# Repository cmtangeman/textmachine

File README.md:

# TextMachine
CrankPhone SW/FW/HW/Mech
Notes on directory structure:

FW:

ArduinoILI9341MKNNB1500 :  All for resistive touch FW (old)

capTouchTestingAndCal: testing calibration of capacitive touch

receiveSMSwithDebug:  debug file that doesn't need touchscreen

techmach: FW for old resistive screen

techmachcap: FW for current working capacitive touch screen.  See README.txt in this directory for further info.

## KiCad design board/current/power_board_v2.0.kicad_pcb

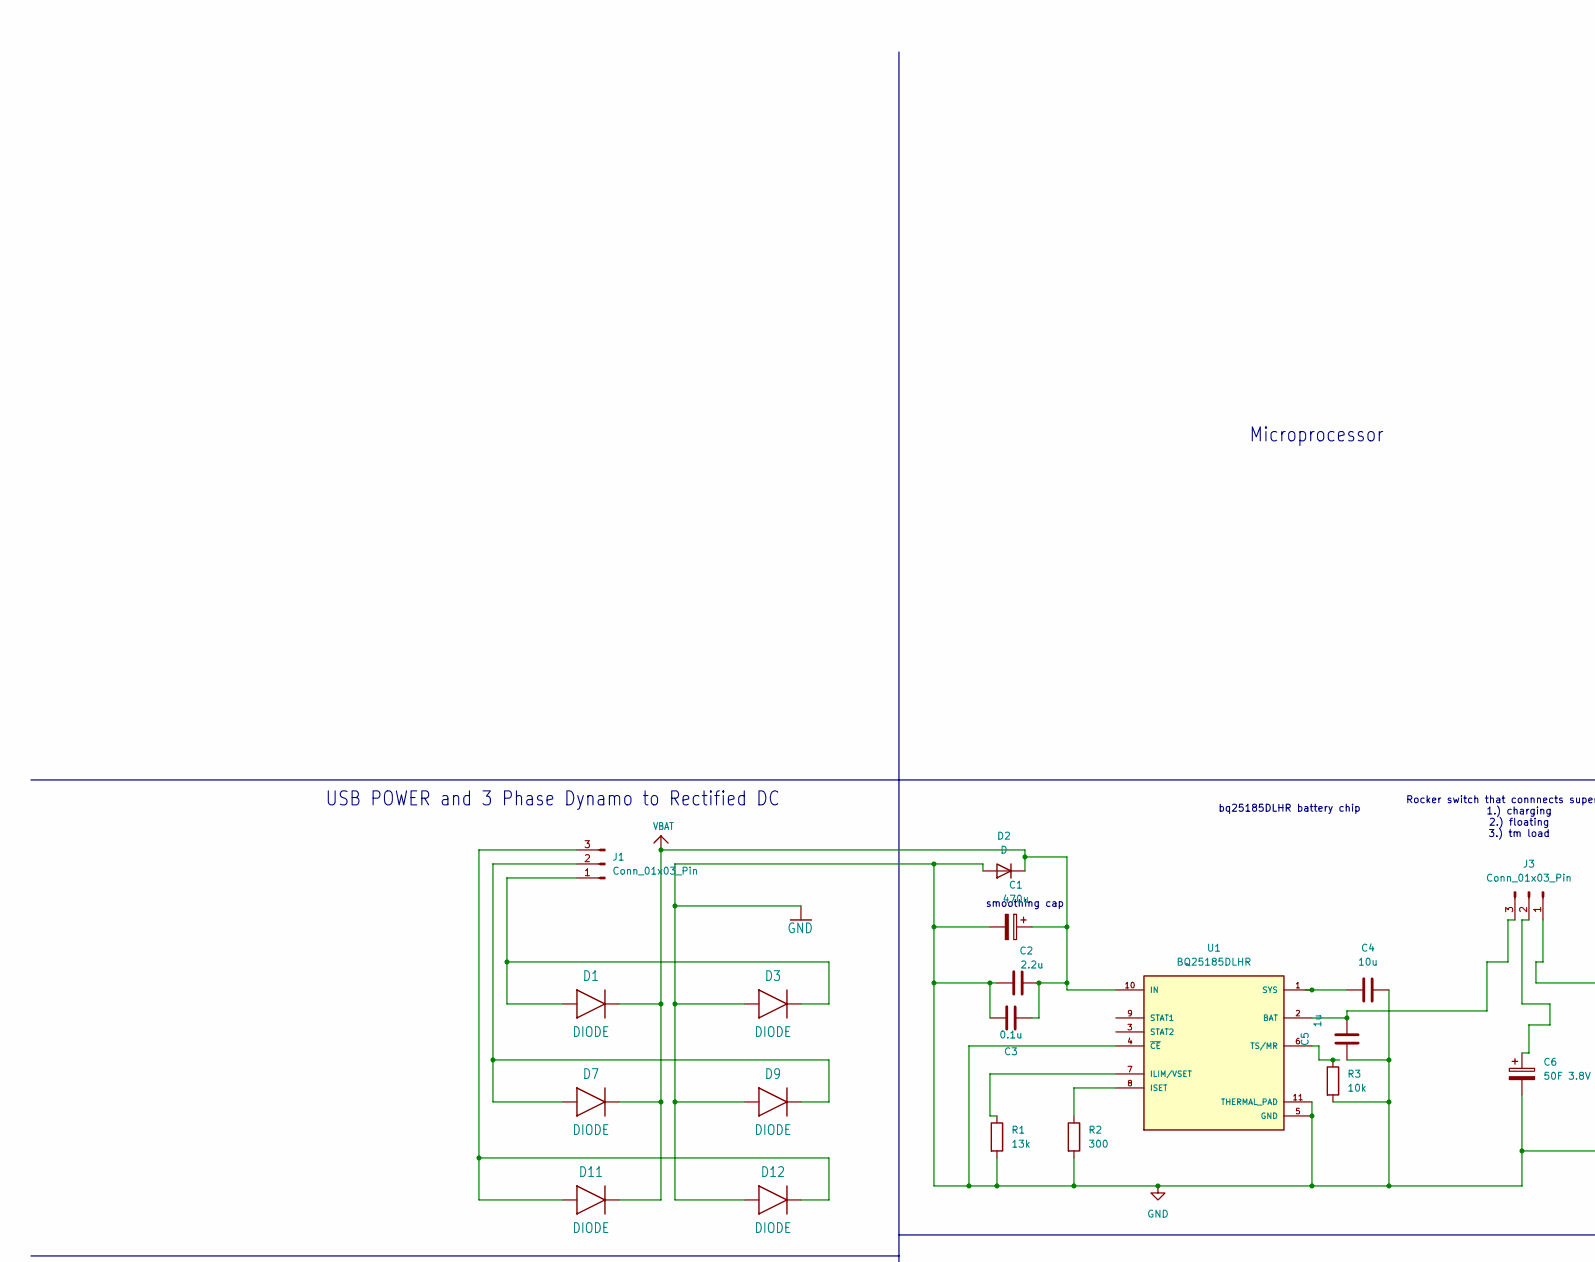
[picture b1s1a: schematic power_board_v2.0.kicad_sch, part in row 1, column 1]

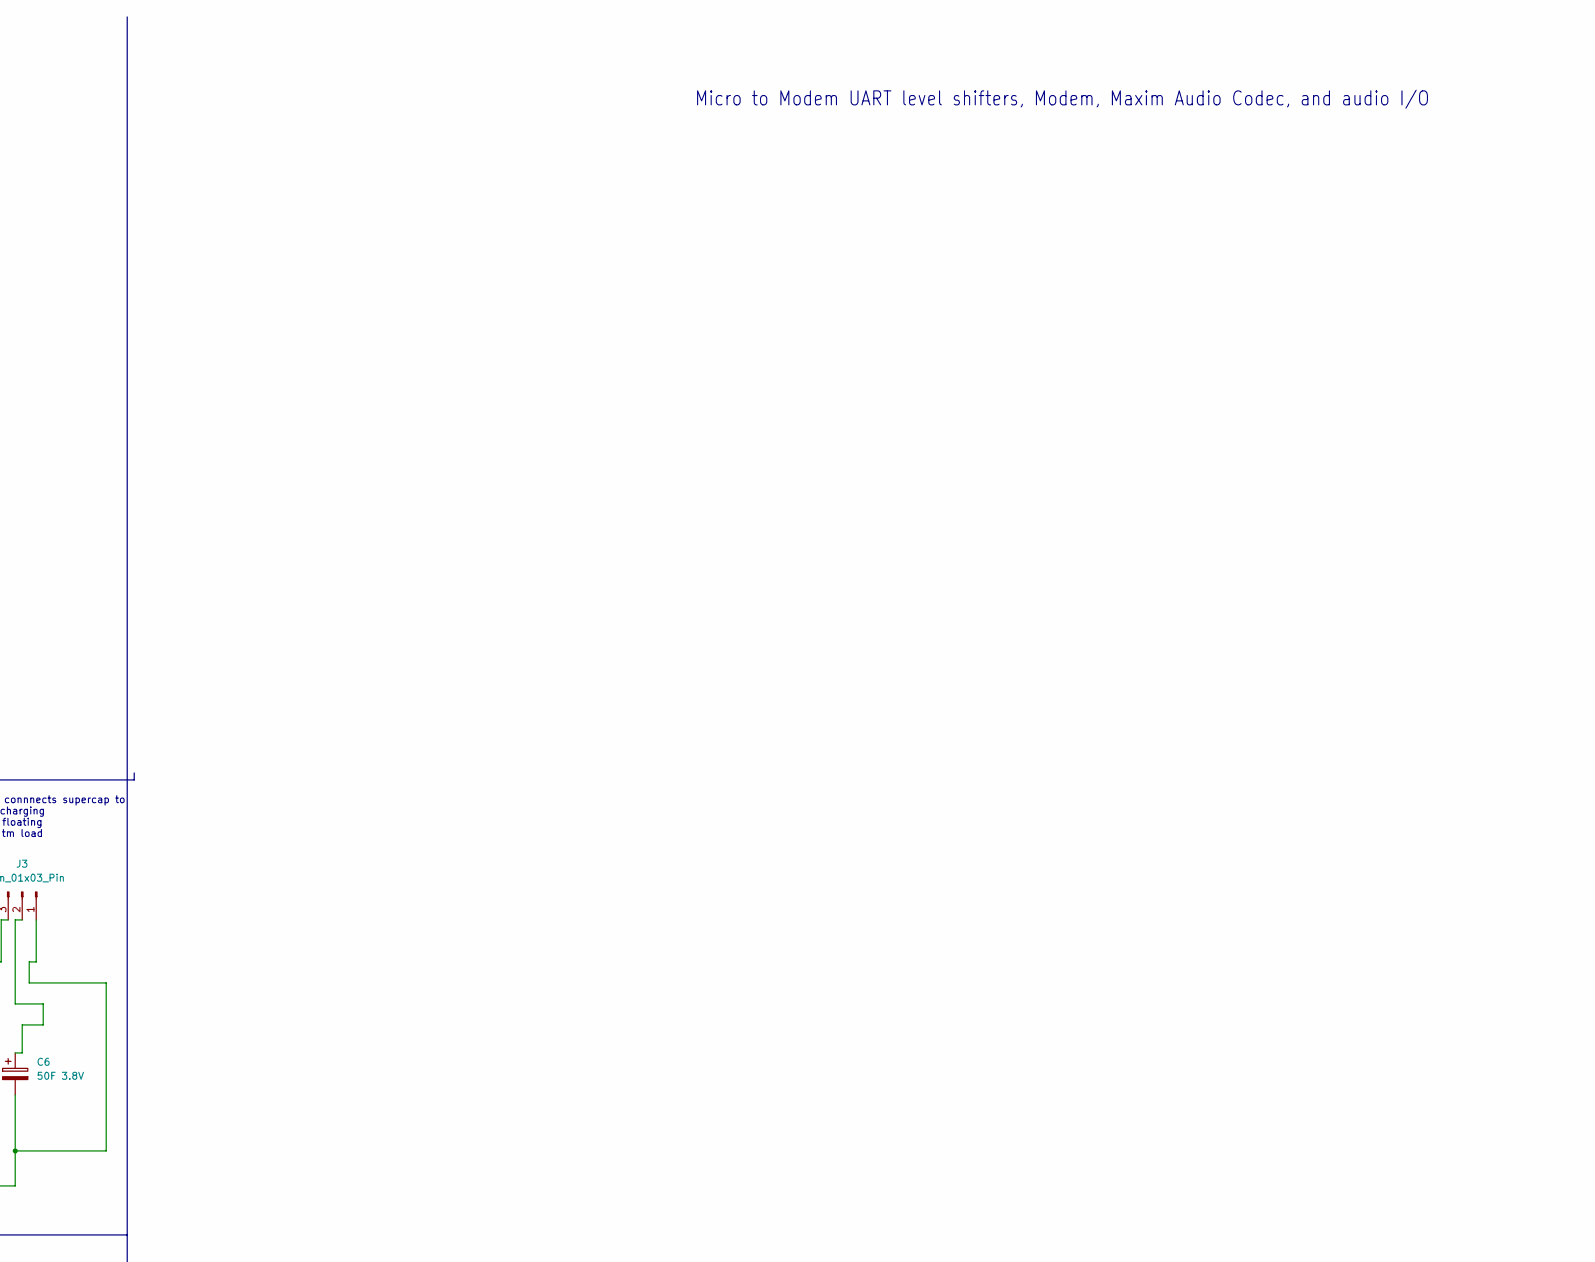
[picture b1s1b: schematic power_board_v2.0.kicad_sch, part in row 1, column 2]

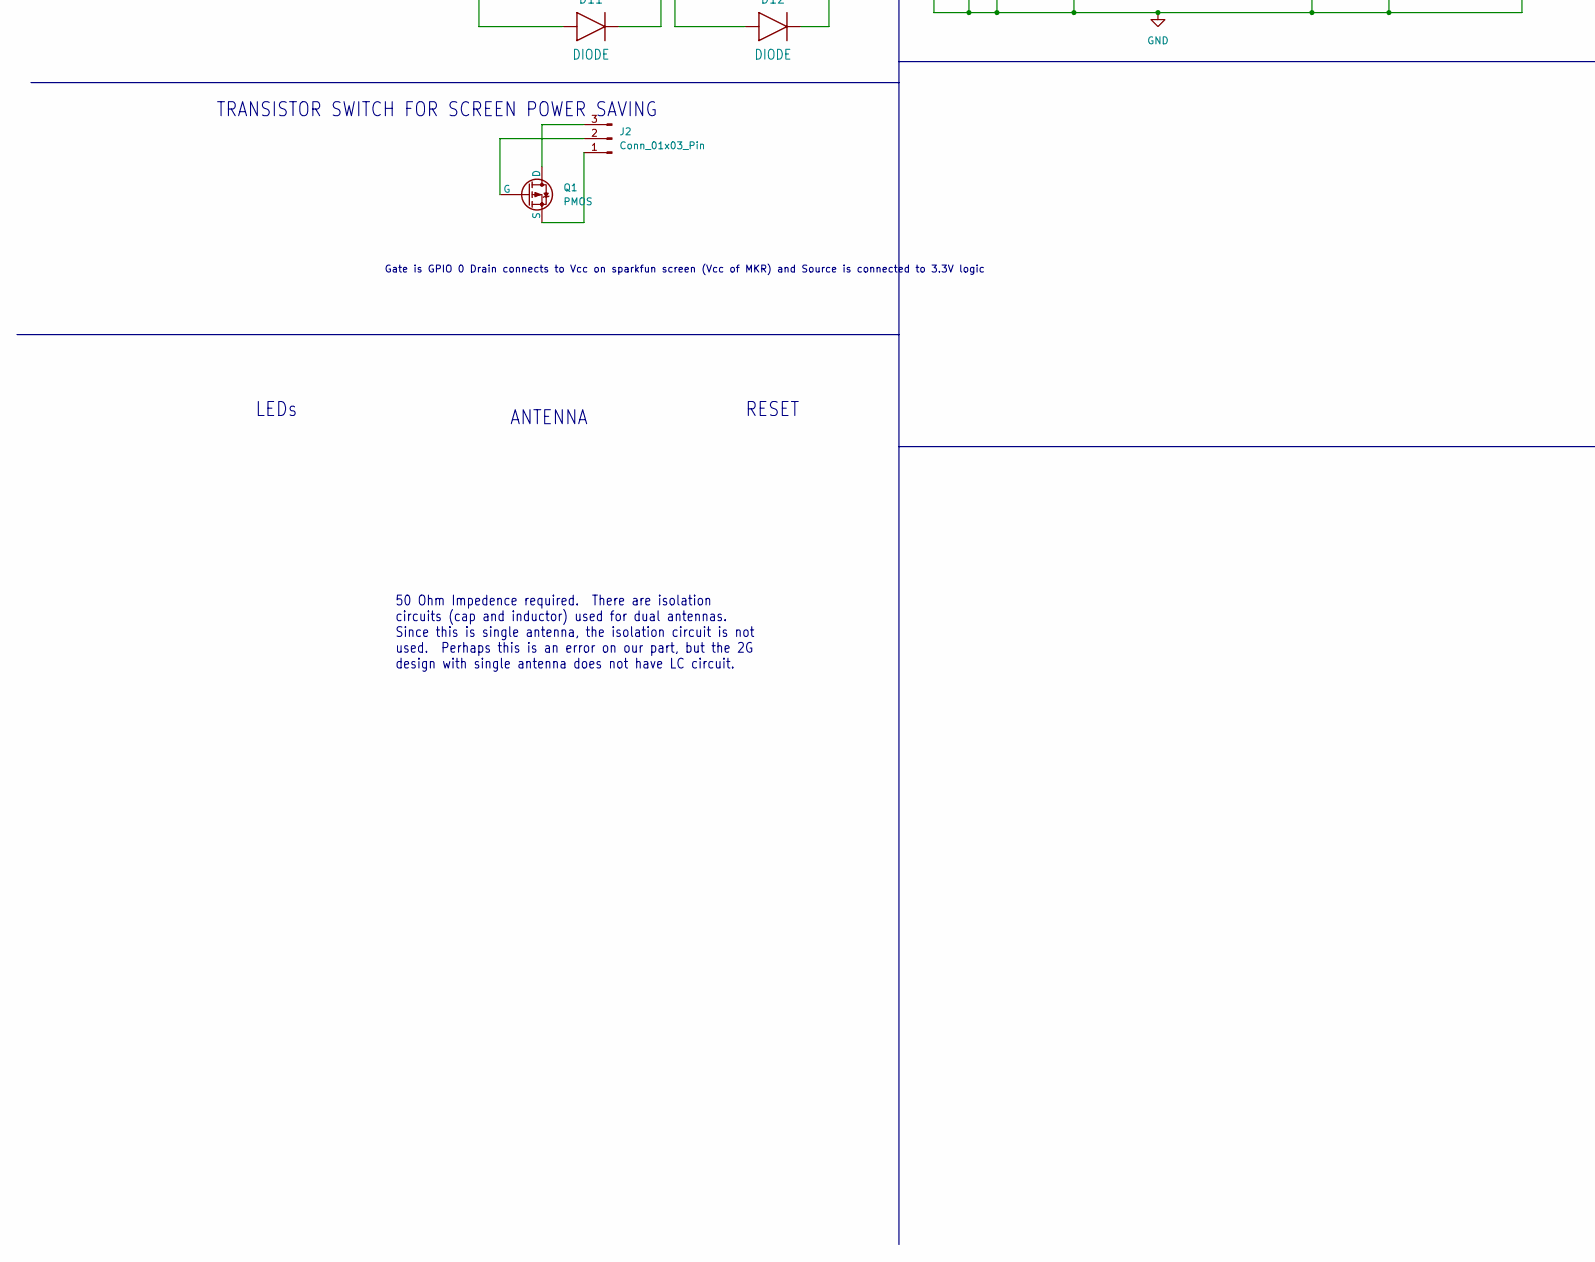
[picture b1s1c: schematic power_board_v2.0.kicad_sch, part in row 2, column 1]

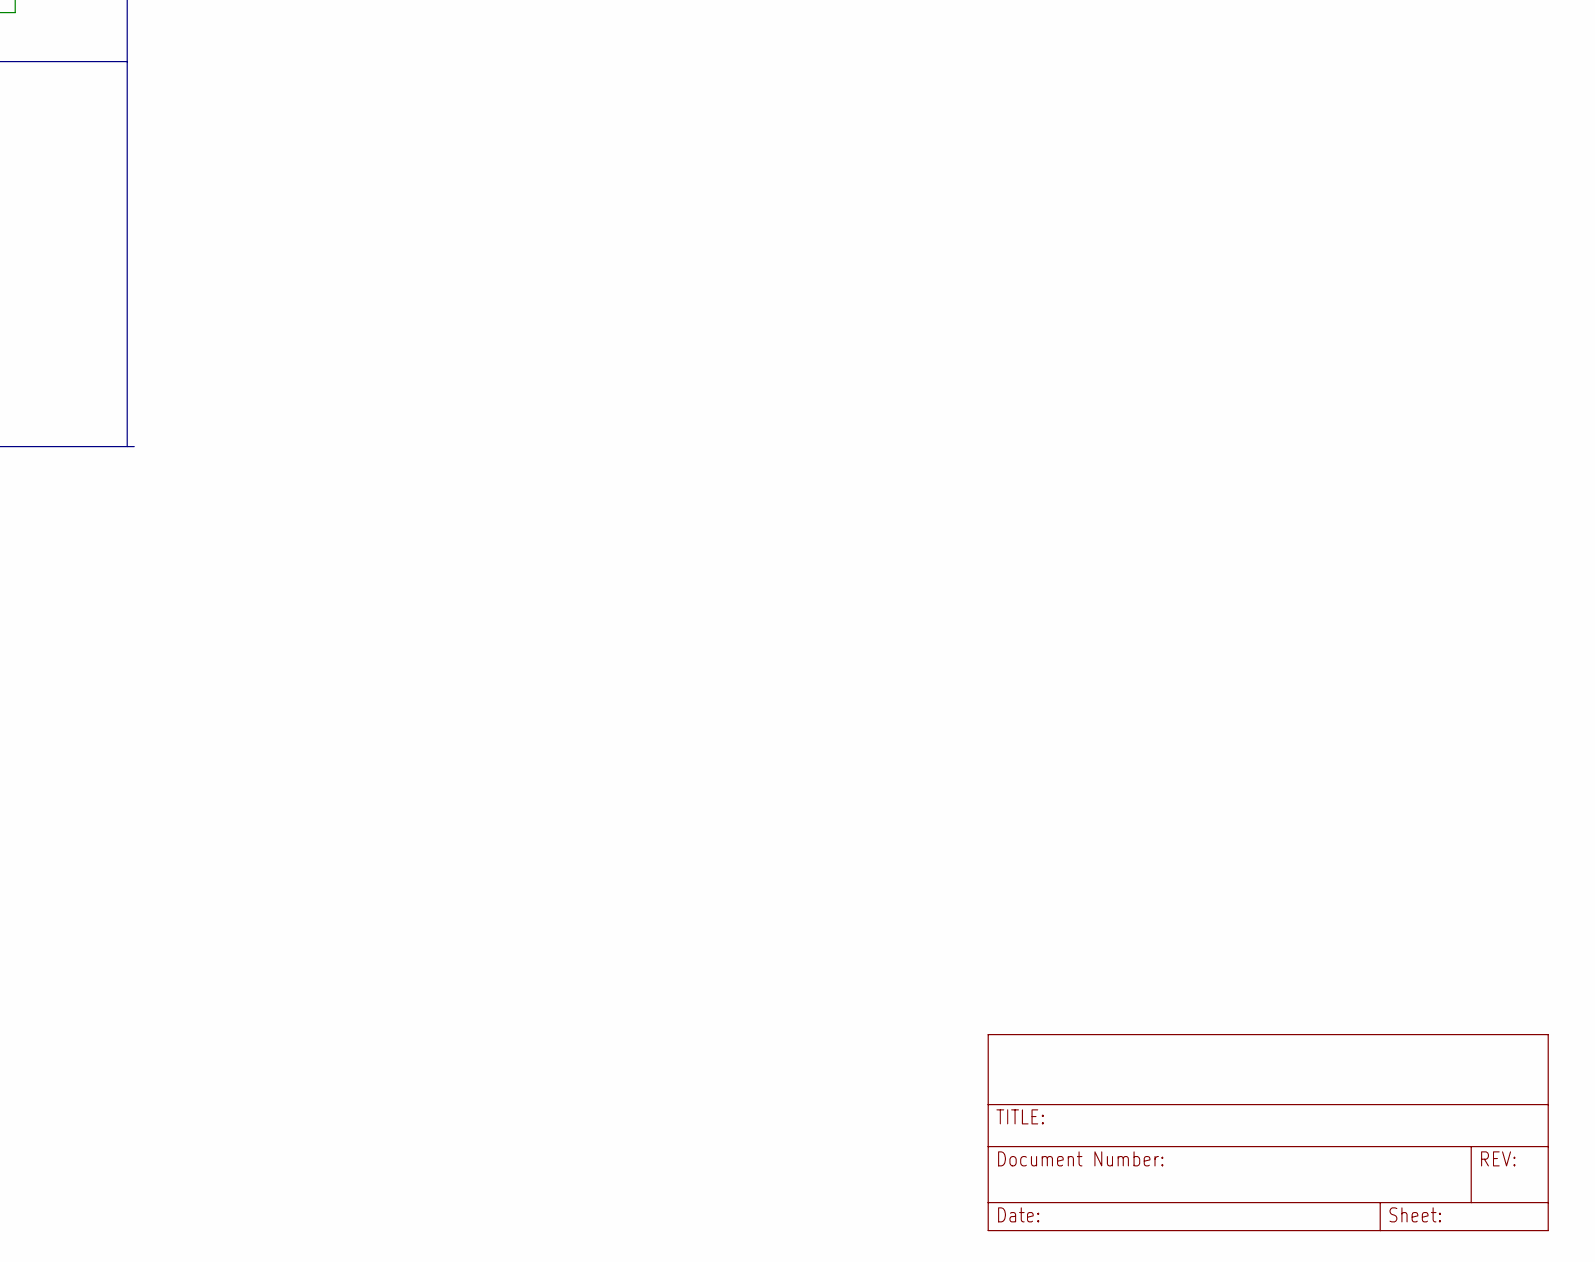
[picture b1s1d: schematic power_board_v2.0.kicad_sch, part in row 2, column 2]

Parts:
C1: 470u; CP_Radial_D8.0mm_P5.00mm
C2: 2.2u; C_0402_1005Metric
C3: 0.1u; C_0402_1005Metric
C4: 10u; C_0402_1005Metric
C5: 1u; C_0402_1005Metric
C6: 50F 3.8V; CP_Radial_D10.0mm_P5.00mm
D1, D3, D7, D9, D11, D12: DIODE; D_SMB
D2: D; D_DO-15_P10.16mm_Horizontal
J1, J2, J3: Conn_01x03_Pin; PinHeader_1x03_P2.54mm_Vertical
Q1: PMOS; SOT-23
R1: 13k; R_0603_1608Metric
R2: 300; R_0603_1608Metric
R3: 10k; R_0603_1608Metric
U1: BQ25185DLHR; Texas_DLH0010A_WSON-10-1EP_2.2x2mm_P0.4mm_EP0.9x1.5mm; PARTREV OCTOBER 2023

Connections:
GND: C1.2, C2.1, C3.1, C4.2, C5.1, C6.2, D2.2 (A), D3.2 (A), D9.2 (A), D12.2 (A), J3.1, R1.2, R2.2, R3.2, U1.4 (~CE), U1.5 (GND), U1.11 (THERMAL_PAD)
unnamed: D1.2 (A), D3.1 (C), J1.1
unnamed: D7.2 (A), D9.1 (C), J1.2
unnamed: D11.2 (A), D12.1 (C), J1.3
unnamed: J2.1, Q1.3 (S)
unnamed: J2.2, Q1.2 (G)
unnamed: J2.3, Q1.1 (D)
unnamed: C6.1, J3.2
unnamed: C5.2, J3.3, U1.2 (BAT)
unnamed: R1.1, U1.7 (ILIM/VSET)
unnamed: R2.1, U1.8 (ISET)
unnamed: C4.1, U1.1 (SYS)
unnamed: R3.1, U1.6 (TS/MR)
VBAT: C1.1, C2.2, C3.2, D1.1 (C), D2.1 (K), D7.1 (C), D11.1 (C), U1.10 (IN)

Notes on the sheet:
Gate is GPIO 0 Drain connects to Vcc on sparkfun screen (Vcc of MKR) and Source is connected to 3.3V logic
Rocker switch that connnects supercap to 1.) charging 2.) floating 3.) tm load
smoothing cap
50 Ohm Impedence required. There are isolation circuits (cap and inductor) used for dual antennas. Since this is single antenna, the isolation circuit is not used. Perhaps this is an error on our part, but the 2G design with single antenna does not have LC circuit.
Micro to Modem UART level shifters, Modem, Maxim Audio Codec, and audio I/O
bq25185DLHR battery chip
RESET
USB POWER and 3 Phase Dynamo to Rectified DC
ANTENNA
TRANSISTOR SWITCH FOR SCREEN POWER SAVING
Microprocessor
LEDs

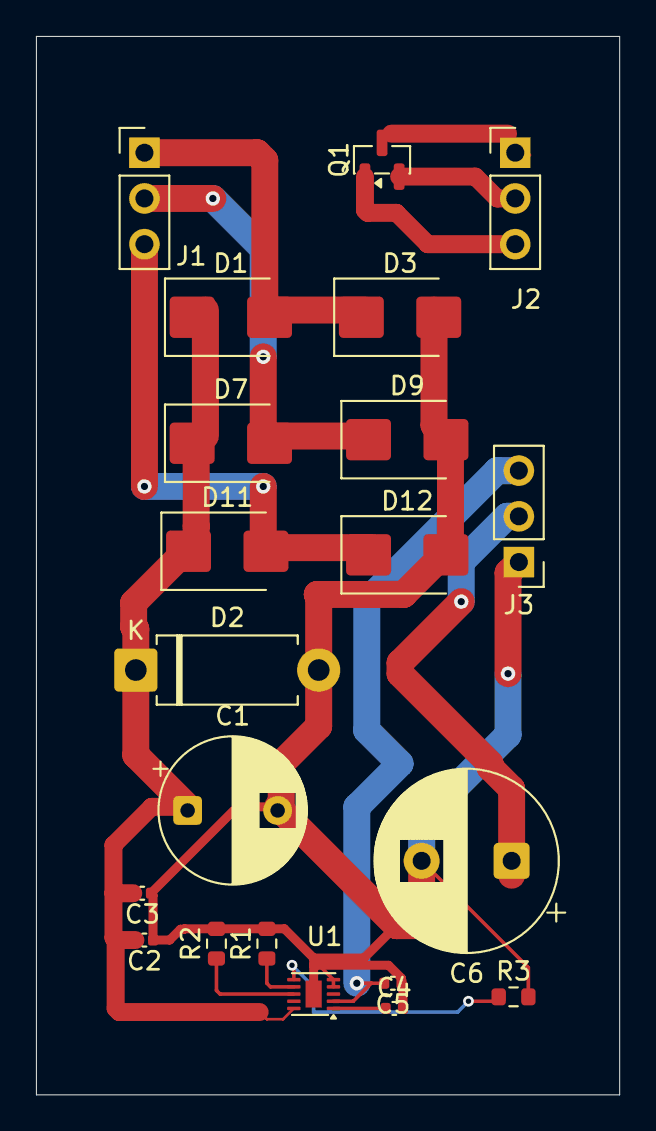
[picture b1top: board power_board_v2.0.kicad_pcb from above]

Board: 2 copper layers, 32.4 x 58.8 mm, 21 parts (0 on the bottom side), 14 nets.
